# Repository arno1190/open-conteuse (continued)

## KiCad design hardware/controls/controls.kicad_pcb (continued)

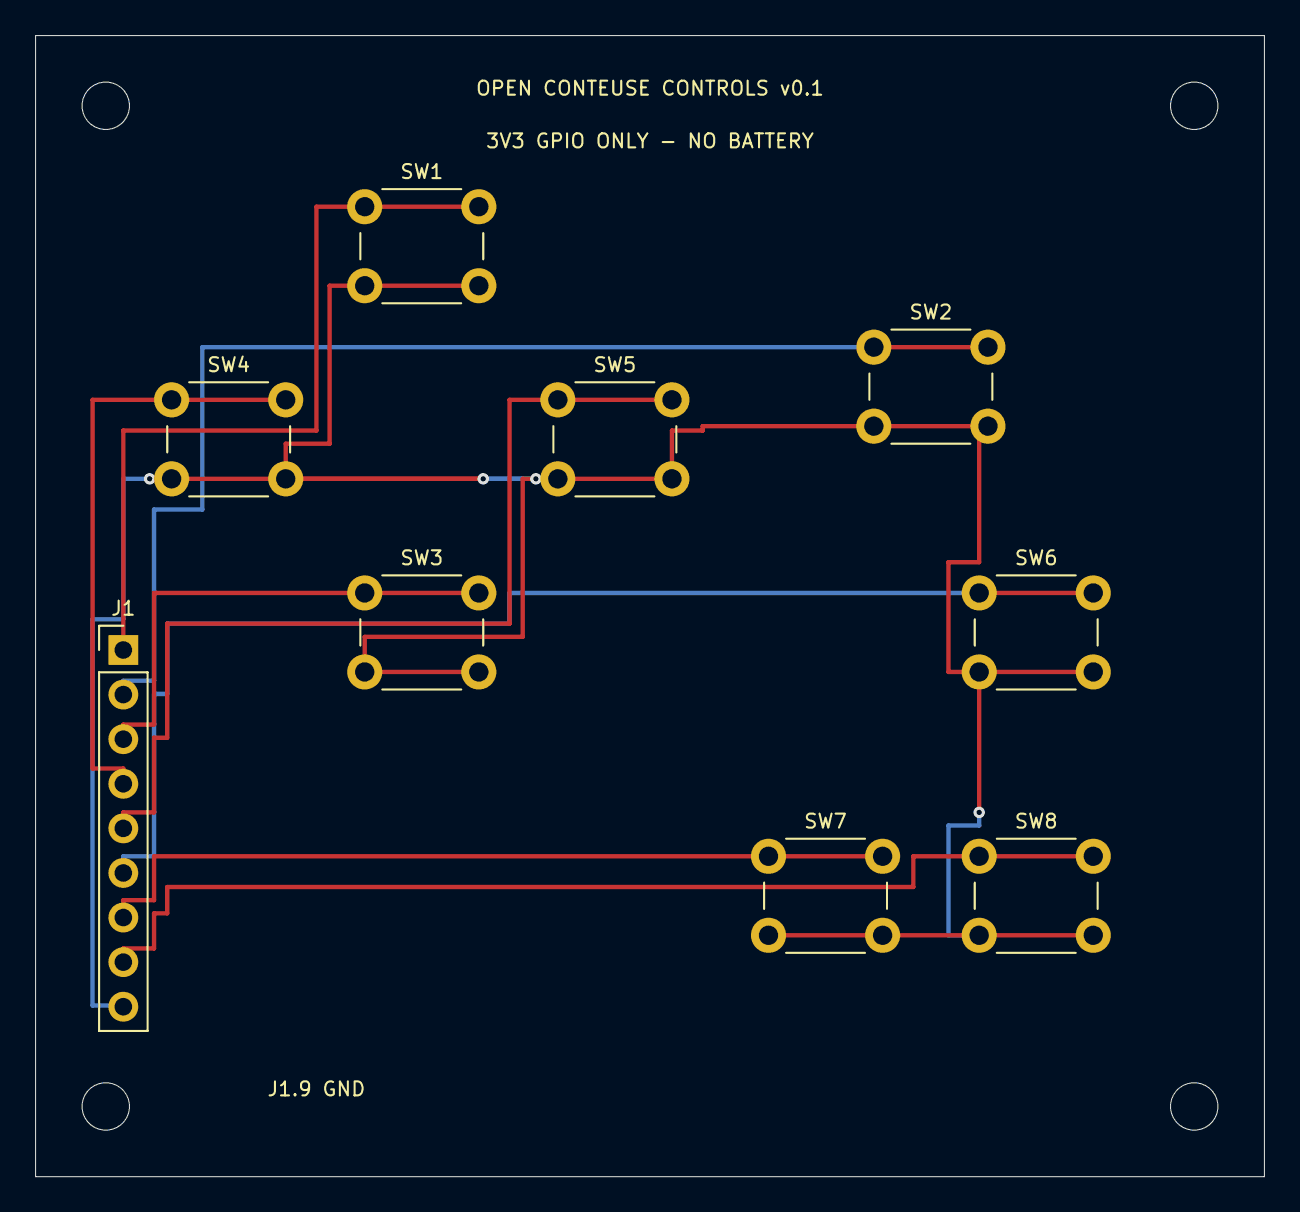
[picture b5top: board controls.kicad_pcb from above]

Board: 2 copper layers, 70.0 x 65.0 mm, 13 parts (0 on the bottom side), 9 nets.

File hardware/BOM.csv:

Reference,Quantity,Variant,Manufacturer,Exact part or module,Role,Status,Source
SW1-SW8,8,Explore,Omron,B3F-1000,6 mm through-hole controls,Footprint geometry assumed; verify drawing and actuator height,https://components.omron.com/us-en/products/switches/B3F
SW2 SW4 SW5 SW7 SW8,5,Mini,Omron,B3F-1000,Populate only Mini controls,Same PCB; other switches DNP,https://components.omron.com/us-en/products/switches/B3F
J1,1,Both,Samtec,TSW-109-07-G-S,1x9 2.54 mm male header,Verify mating height; keyed harness preferred before child use,https://www.samtec.com/products/tsw
PCB,1,Both,Unassigned,controls v0.1 70x65x1.6 mm 2 layers,Passive controls daughterboard,ERC/DRC checked; NOT ordered,hardware/controls/controls.kicad_pcb
MCU,1,Both,Espressif,ESP32-S3-DevKitC-1 with ESP32-S3-WROOM-1-N16R8,USB-powered bench controller,Exact module marking must be checked before flashing,https://docs.espressif.com/projects/esp-dev-kits/en/latest/e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
SD,1,Both,Adafruit,MicroSD SPI or SDIO breakout 3V ONLY product 4682,3.3 V removable storage,Wire harness prototype; dimensions unmeasured,https://www.adafruit.com/product/4682
NFC,1,Mini; optional Explore,Adafruit,PN532 breakout product 364 in I2C mode,Card reader,Verify revision and I2C jumpers; no antenna metal in front,https://www.adafruit.com/product/364
TFT,1,Explore,Adafruit,2.8 inch ILI9341 resistive touchscreen breakout product 1770,320x240 display; touch unused,Only display driver integrated; module fit unmeasured,https://www.adafruit.com/product/1770
DAC,1,Both bench,Adafruit,UDA1334A I2S stereo decoder product 3678,Line-level stereo bench output,NOT a headphone driver; power and wiring review pending,https://www.adafruit.com/product/3678
AMP,1,Both bench,Adafruit,MAX98357A I2S amplifier product 3006,Separate mono speaker output,Requires shutdown pulldown and independent jack mute; keep disconnected initially,https://www.adafruit.com/product/3006
R_MUTE,1,Both bench,Any qualified supplier,10k ohm 1 percent resistor,External amplifier shutdown pulldown,Not on passive controls PCB; must be fitted in bench harness,hardware/ASSEMBLY.md
HEADPHONE,1,Both,Texas Instruments,TPA6132A2EVM candidate,Headphone amplifier evaluation,NOT selected for enclosure or wired by this design; review single-ended inputs gain jack mute,https://www.ti.com/tool/TPA6132A2EVM
JACK,1,Both,Unselected,3.5 mm stereo with independently verified insertion detection,Stereo headphone socket,Blocked on exact jack and analogue interface review,hardware/README.md
SPEAKER,1,Both,Unselected,40 mm nominal diameter 4 ohm candidate,Speech output,Impedance depth excursion acoustic gain and retention pending,hardware/README.md
BATTERY,1,Both,Unselected,Protected 1S replaceable pack 2500-3500 mAh target,Battery supply,NO battery wiring or charge design released,hardware/README.md
CHARGER,1,Both,Texas Instruments,BQ24074 candidate with power path,Charger candidate only,Input current CC protection thermal and regulator design pending,https://www.ti.com/product/BQ24074
FRONT,1,Both,Original design,shell.scad front,Variant front with controls and screen/card opening,100x174x19 mm provisional; not printed,enclosure/shell.scad
BACK,1,Both,Original design,shell.scad back,Common screw-retained back,100x174x19 mm provisional; not printed,enclosure/shell.scad
PLUNGER,5 or 8,Both,Original design,shell.scad plunger,Captive button actuator,Travel flange and clearance must be fit tested,enclosure/shell.scad
FASTENERS,8,Both,Unselected,M2.5 screws; 4 PCB and 4 case,Serviceable fastening,Lengths pilot fit thread engagement and retention pending,enclosure/DIMENSIONS.md
